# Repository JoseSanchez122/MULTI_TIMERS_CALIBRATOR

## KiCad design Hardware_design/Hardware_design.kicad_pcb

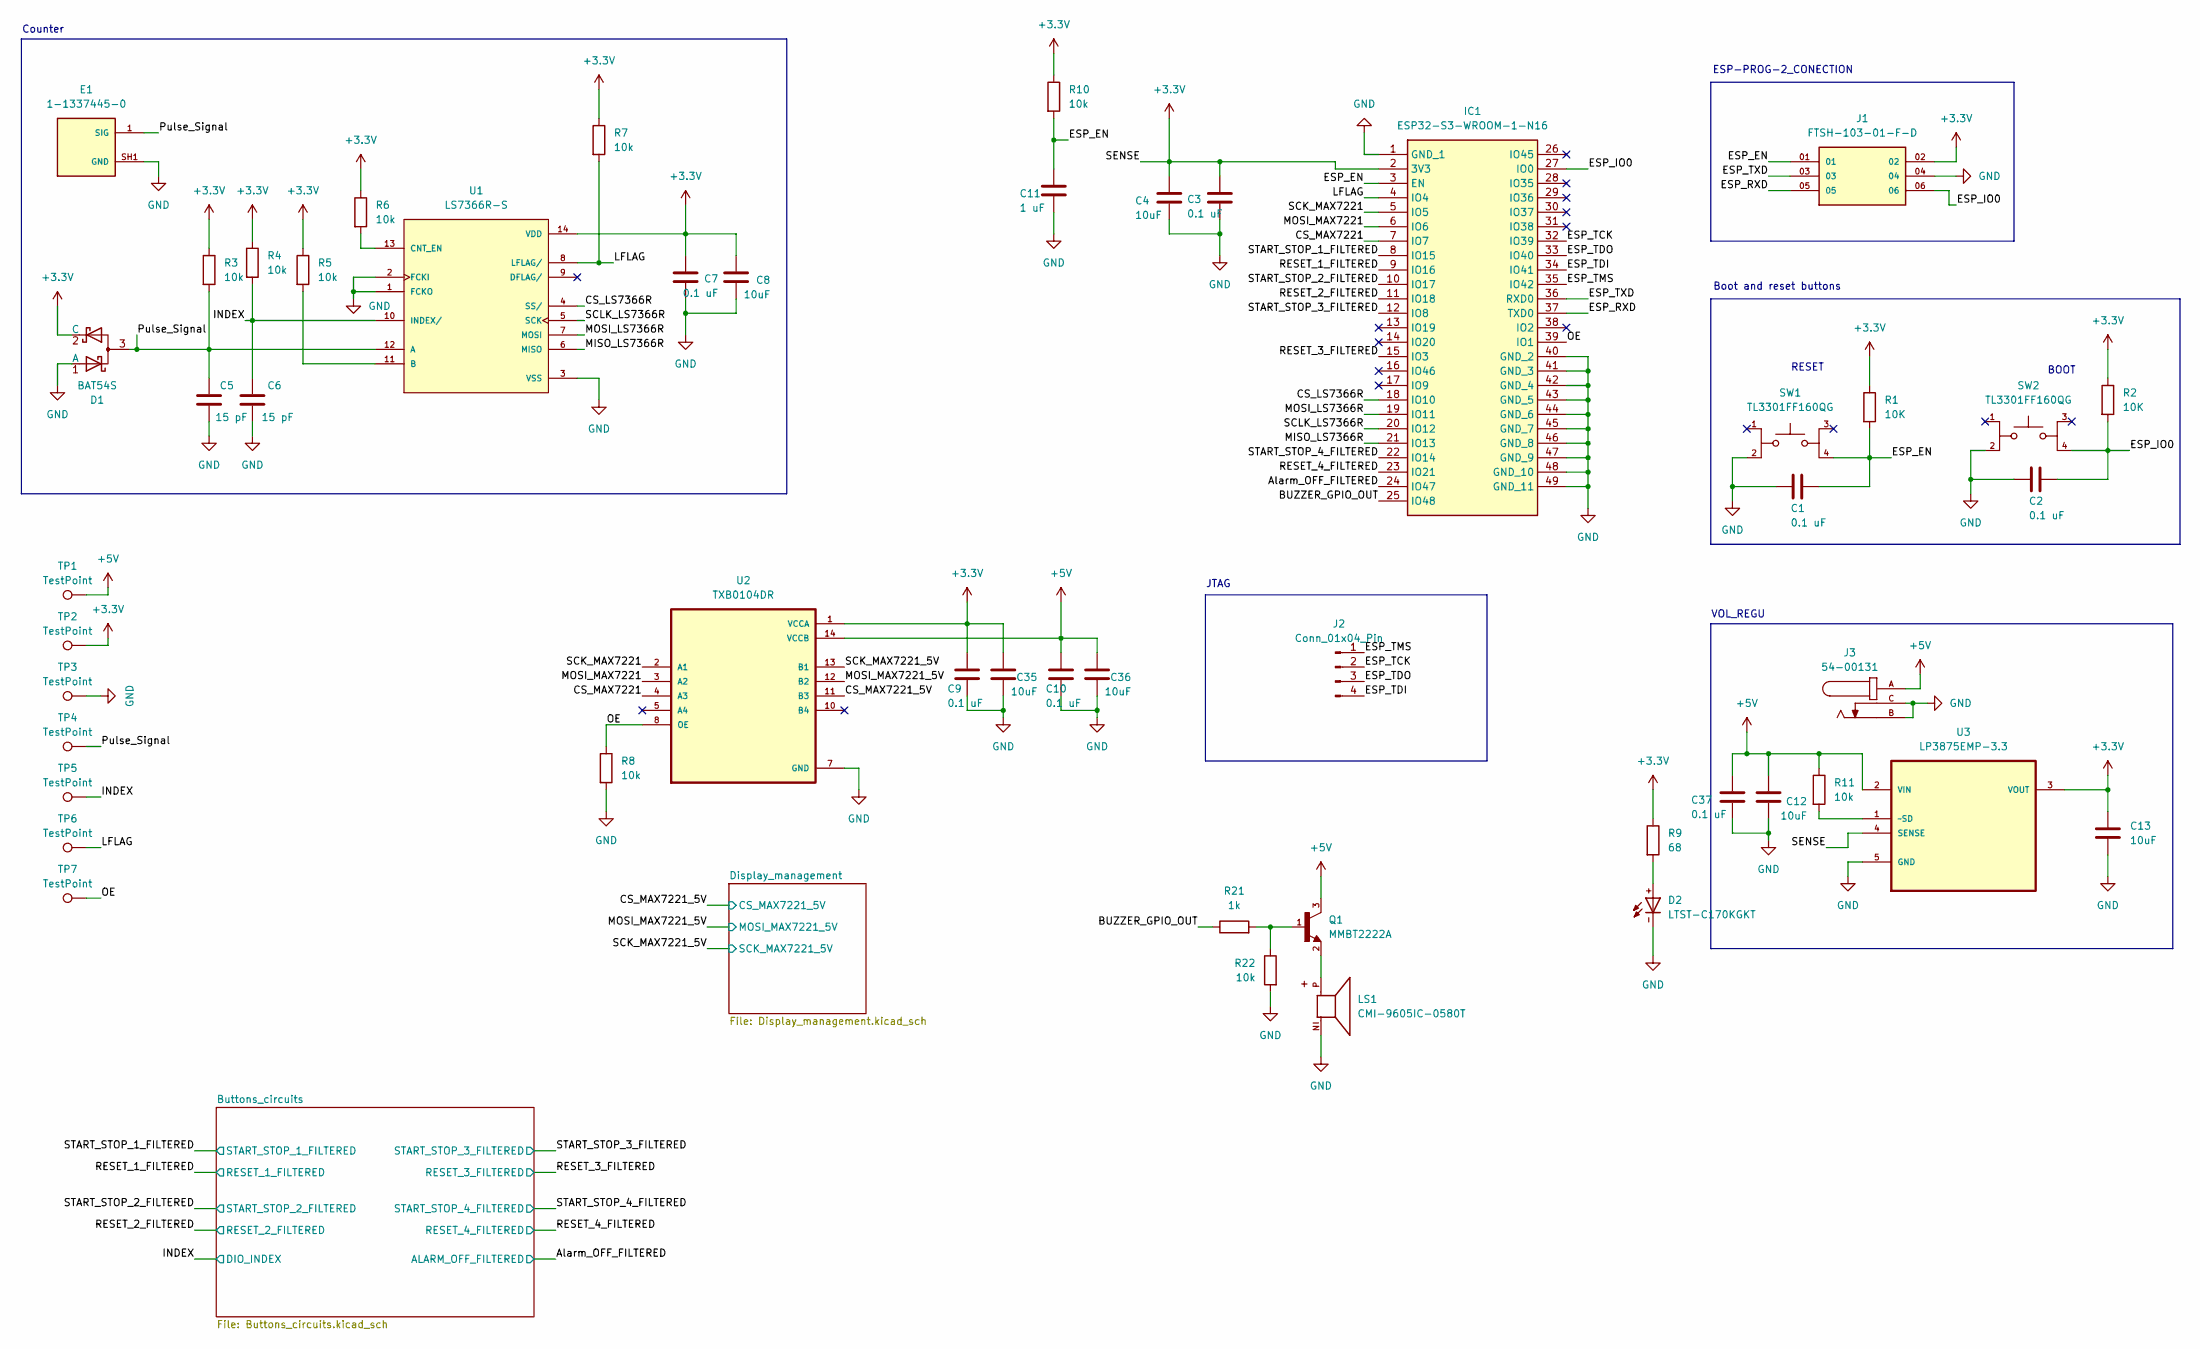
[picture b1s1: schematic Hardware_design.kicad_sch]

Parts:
C1, C2, C3, C7, C9, C10, C37: 0.1 uF; 0805_SMD_CERAMIC_CAP_T491B106K016AT
C4, C8, C12, C13, C35, C36: 10uF; 0805_SMD_TANT_CAP_T491B106K016AT
C5, C6: 15 pF; 0805_SMD_CERAMIC_CAP_T491B106K016AT
C11: 1 uF; CAP_0603_CAPC1608X90N
D1: BAT54S; Schottky_diode_BAT54S
D2: LTST-C170KGKT; GREEN_LED_LTST-C170KGKT; DigiKey_Part_Number 160-1414-1-ND
E1: 1-1337445-0; VNC_CONECTOR_1-1337445-0; PARTREV C
IC1: ESP32-S3-WROOM-1-N16; ESP32S3WROOM1N16; Mouser Part Number 356-ESP32S3WROOM1N16
J1: FTSH-103-01-F-D; PROG_CONECTOR_SAMTEC_FTSH-103-01-F-D; PARTREV B
J2: Conn_01x04_Pin; 4_pin_FTR-104-01-L-S
J3: 54-00131; POWER_CONE_54-00131; PARTREV A
LS1: CMI-9605IC-0580T; BUZZER_CMI-9605IC-0580T; PARTREV 1.0
Q1: MMBT2222A; TRANSISTOR_MMBT2222A; PARTREV 2024-03-11
R1, R2: 10K; 0805_RES_RESC2012X60N
R3, R4, R5, R6, R7, R8, R10, R11, R22: 10k; 0805_RES_RESC2012X60N
R9: 68; 0805_RES_RESC2012X60N
R21: 1k; 0805_RES_RESC2012X60N
SW1, SW2: TL3301FF160QG; BUTTON_TL3301FF160QG; PARTREV E
TP1, TP2, TP3, TP4, TP5, TP6, TP7: TestPoint; TestPoint_Pad_1.0x1.0mm
U1: LS7366R-S; PARTREV June 2014
U2: TXB0104DR; LEVEL_SHIFTER_TXB0104DR
U3: LP3875EMP-3.3; V_REGU_LP3875EMP-3.3; MPN LP3875EMP-3.3

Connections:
+3.3V: C3.1, C4.1, C7.1, C8.1, C9.1, C13.1, C35.1, D1.2 (C), IC1.2 (3V3), J1.02, R1.1, R2.1, R3.1, R4.1, R5.1, R6.1, R7.1, R9.1, R10.1, TP2.1 (1_1), U1.14 (VDD), U2.1 (VCCA), U3.3 (VOUT), U3.4 (SENSE); also elsewhere on the board
+5V: C10.1, C12.1, C36.1, C37.1, J3.A, Q1.3, R11.1, TP1.1 (1_1), U2.14 (VCCB), U3.2 (VIN); also elsewhere on the board
/Alarm_OFF_FILTERED: IC1.24 (IO47); also elsewhere on the board
/BUZZER_GPIO_OUT: IC1.25 (IO48), R21.1
/CS_LS7366R: IC1.18 (IO10), U1.4 (SS/)
/CS_MAX7221: IC1.7 (IO7), U2.4 (A3)
/CS_MAX7221_5V: U2.11 (B3); also elsewhere on the board
/ESP_EN: C1.1, C11.1, IC1.3 (EN), J1.01, R1.2, R10.2, SW1.4
/ESP_IO0: C2.1, IC1.27 (IO0), J1.06, R2.2, SW2.4
/ESP_RXD: IC1.37 (TXD0), J1.05
/ESP_TCK: IC1.32 (IO39), J2.2
/ESP_TDI: IC1.34 (IO41), J2.4
/ESP_TDO: IC1.33 (IO40), J2.3
/ESP_TMS: IC1.35 (IO42), J2.1
/ESP_TXD: IC1.36 (RXD0), J1.03
/INDEX: C6.1, R4.2, TP5.1 (1_1), U1.10 (INDEX/); also elsewhere on the board
/LFLAG: IC1.4 (IO4), R7.2, TP6.1 (1_1), U1.8 (LFLAG/)
/MISO_LS7366R: IC1.21 (IO13), U1.6 (MISO)
/MOSI_LS7366R: IC1.19 (IO11), U1.7 (MOSI)
/MOSI_MAX7221: IC1.6 (IO6), U2.3 (A2)
/MOSI_MAX7221_5V: U2.12 (B2); also elsewhere on the board
/OE: IC1.39 (IO1), R8.1, TP7.1 (1_1), U2.8 (OE)
/Pulse_Signal: C5.1, D1.3, E1.1 (SIG), R3.2, TP4.1 (1_1), U1.12 (A)
/RESET_1_FILTERED: IC1.9 (IO16); also elsewhere on the board
/RESET_2_FILTERED: IC1.11 (IO18); also elsewhere on the board
/RESET_3_FILTERED: IC1.15 (IO3); also elsewhere on the board
/RESET_4_FILTERED: IC1.23 (IO21); also elsewhere on the board
/SCK_MAX7221: IC1.5 (IO5), U2.2 (A1)
/SCK_MAX7221_5V: U2.13 (B1); also elsewhere on the board
/SCLK_LS7366R: IC1.20 (IO12), U1.5 (SCK)
/START_STOP_1_FILTERED: IC1.8 (IO15); also elsewhere on the board
/START_STOP_2_FILTERED: IC1.10 (IO17); also elsewhere on the board
/START_STOP_3_FILTERED: IC1.12 (IO8); also elsewhere on the board
/START_STOP_4_FILTERED: IC1.22 (IO14); also elsewhere on the board
GND: C1.2, C2.2, C3.2, C4.2, C5.2, C6.2, C7.2, C8.2, C9.2, C10.2, C11.2, C12.2, C13.2, C35.2, C36.2, C37.2, D1.1 (A), D2.-, E1.SH1 (GND), E1.SH2 (GND), E1.SH3 (GND), E1.SH4 (GND), IC1.1 (GND_1), IC1.40 (GND_2), IC1.41 (GND_3), IC1.42 (GND_4), IC1.43 (GND_5), IC1.44 (GND_6), IC1.45 (GND_7), IC1.46 (GND_8), IC1.47 (GND_9), IC1.48 (GND_10), IC1.49 (GND_11), J1.04, J3.B, J3.C, LS1.N, R8.2, R22.2, SW1.2, SW2.2, TP3.1 (1_1), U1.1 (FCKO), U1.2 (FCKI), U1.3 (VSS), U2.7 (GND), U3.5 (GND); also elsewhere on the board
unnamed: D2.+, R9.2
unnamed: LS1.P, Q1.2
unnamed: Q1.1, R21.2, R22.1
unnamed: R5.2, U1.11 (B)
unnamed: R6.2, U1.13 (CNT_EN)
unnamed: R11.2, U3.1 (~SD)

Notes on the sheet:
BOOT
Boot and reset buttons
VOL_REGU
ESP-PROG-2_CONECTION
RESET
Counter
JTAG
